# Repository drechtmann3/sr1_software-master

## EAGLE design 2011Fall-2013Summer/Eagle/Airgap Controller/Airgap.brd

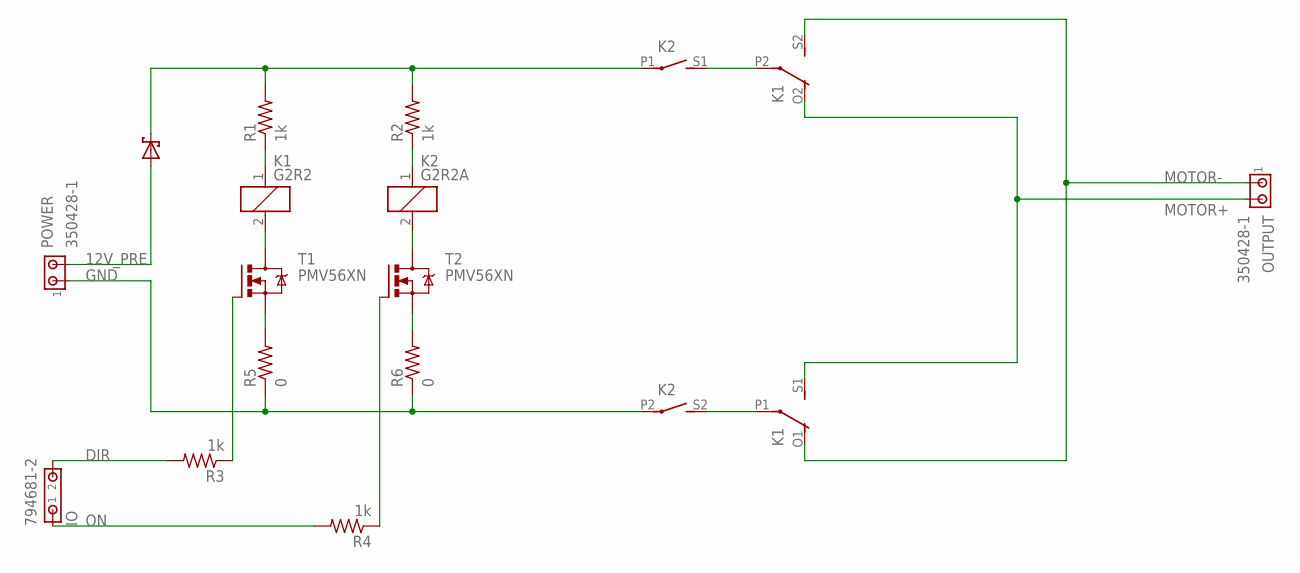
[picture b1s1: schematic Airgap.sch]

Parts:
D3: 6A4; P6T15
IO: 794681-2
K1: G2R2
K2: G2R2A
OUTPUT: 350428-1
POWER: 350428-1
R1, R2, R3, R4: 1k; R1206; PART_NUM CR1206-FX-1001GLF
R5, R6: 0; R1206; PART_NUM CR1206-J/-000ELF
T1, T2: PMV56XN; SOT23

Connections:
12V: D3.C, K2.P1, R1.2, R2.2
12V_PRE: D3.A, POWER.2
DIR: IO.2, R3.2
GND: K2.P2, POWER.1, R5.1, R6.1
MOTOR+: K1.O2 (O), K1.S1 (S), OUTPUT.2
MOTOR-: K1.O1 (O), K1.S2 (S), OUTPUT.1
unnamed: K1.P2, K2.S1 (S)
unnamed: K1.P1, K2.S2 (S)
unnamed: K1.1, R1.1
unnamed: K2.1, R2.1
unnamed: K1.2, T1.3 (D)
unnamed: K2.2, T2.3 (D)
unnamed: R4.1, T2.1 (G)
unnamed: R3.1, T1.1 (G)
unnamed: R5.2, T1.2 (S)
unnamed: R6.2, T2.2 (S)
ON: IO.1, R4.2

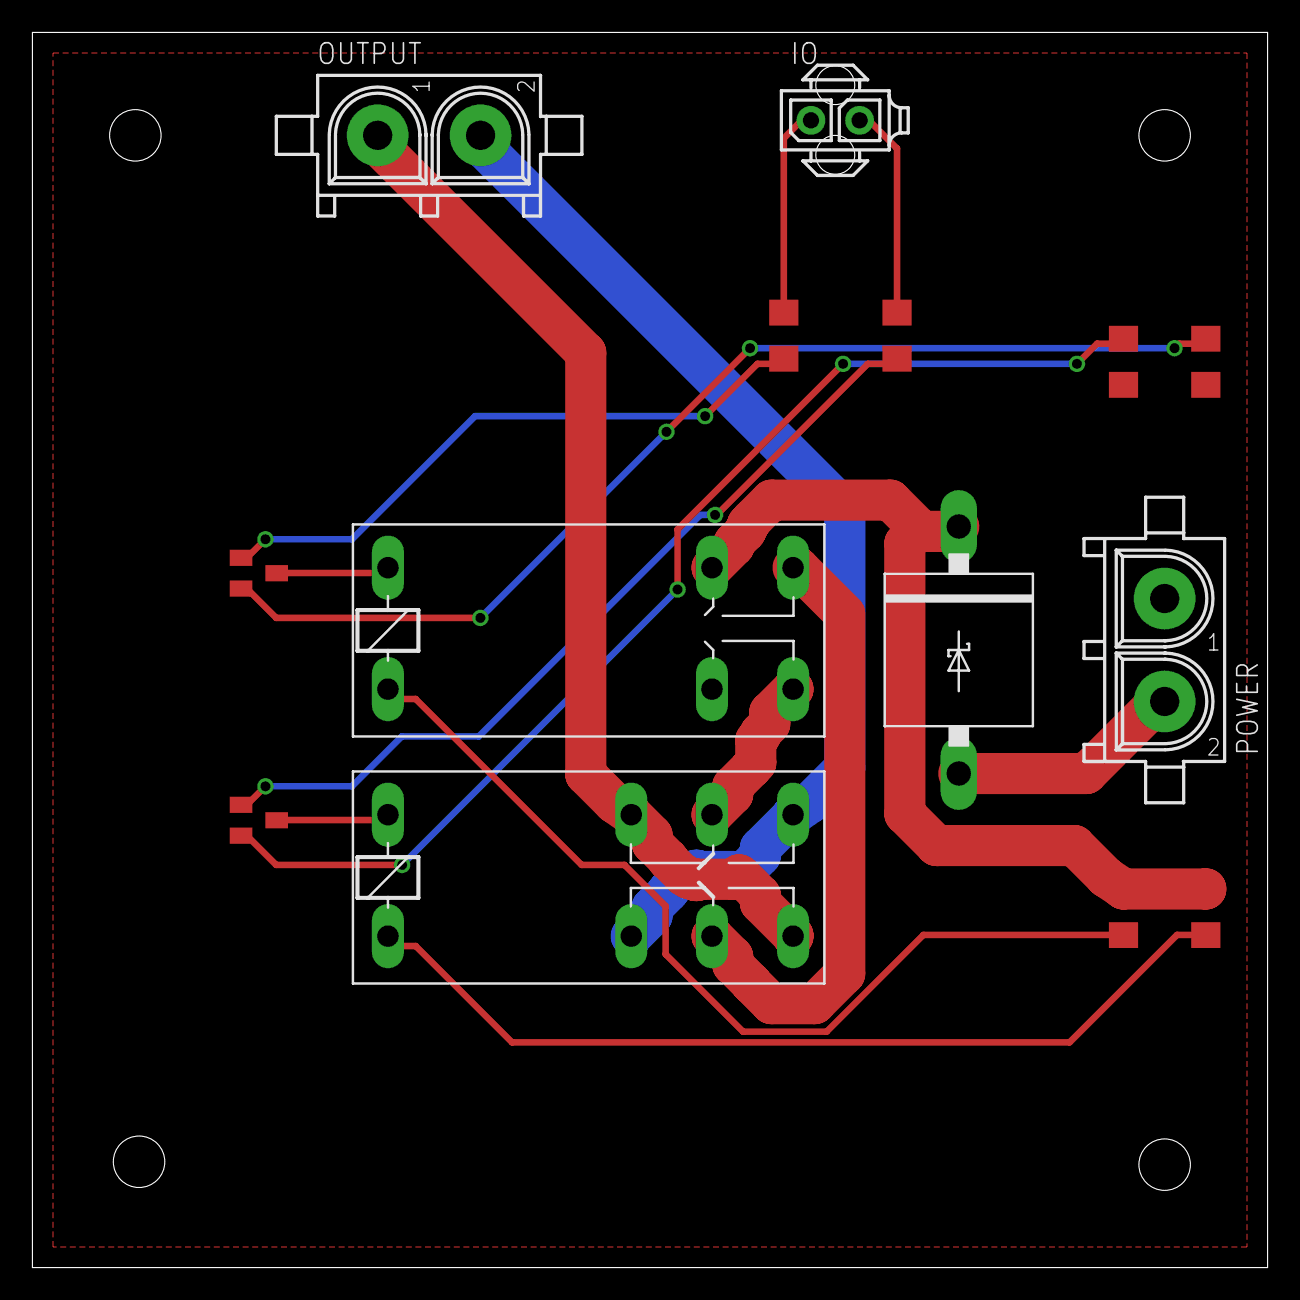
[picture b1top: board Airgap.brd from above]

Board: 2 copper layers, 76.2 x 76.2 mm, 14 parts (0 on the bottom side), 17 nets.

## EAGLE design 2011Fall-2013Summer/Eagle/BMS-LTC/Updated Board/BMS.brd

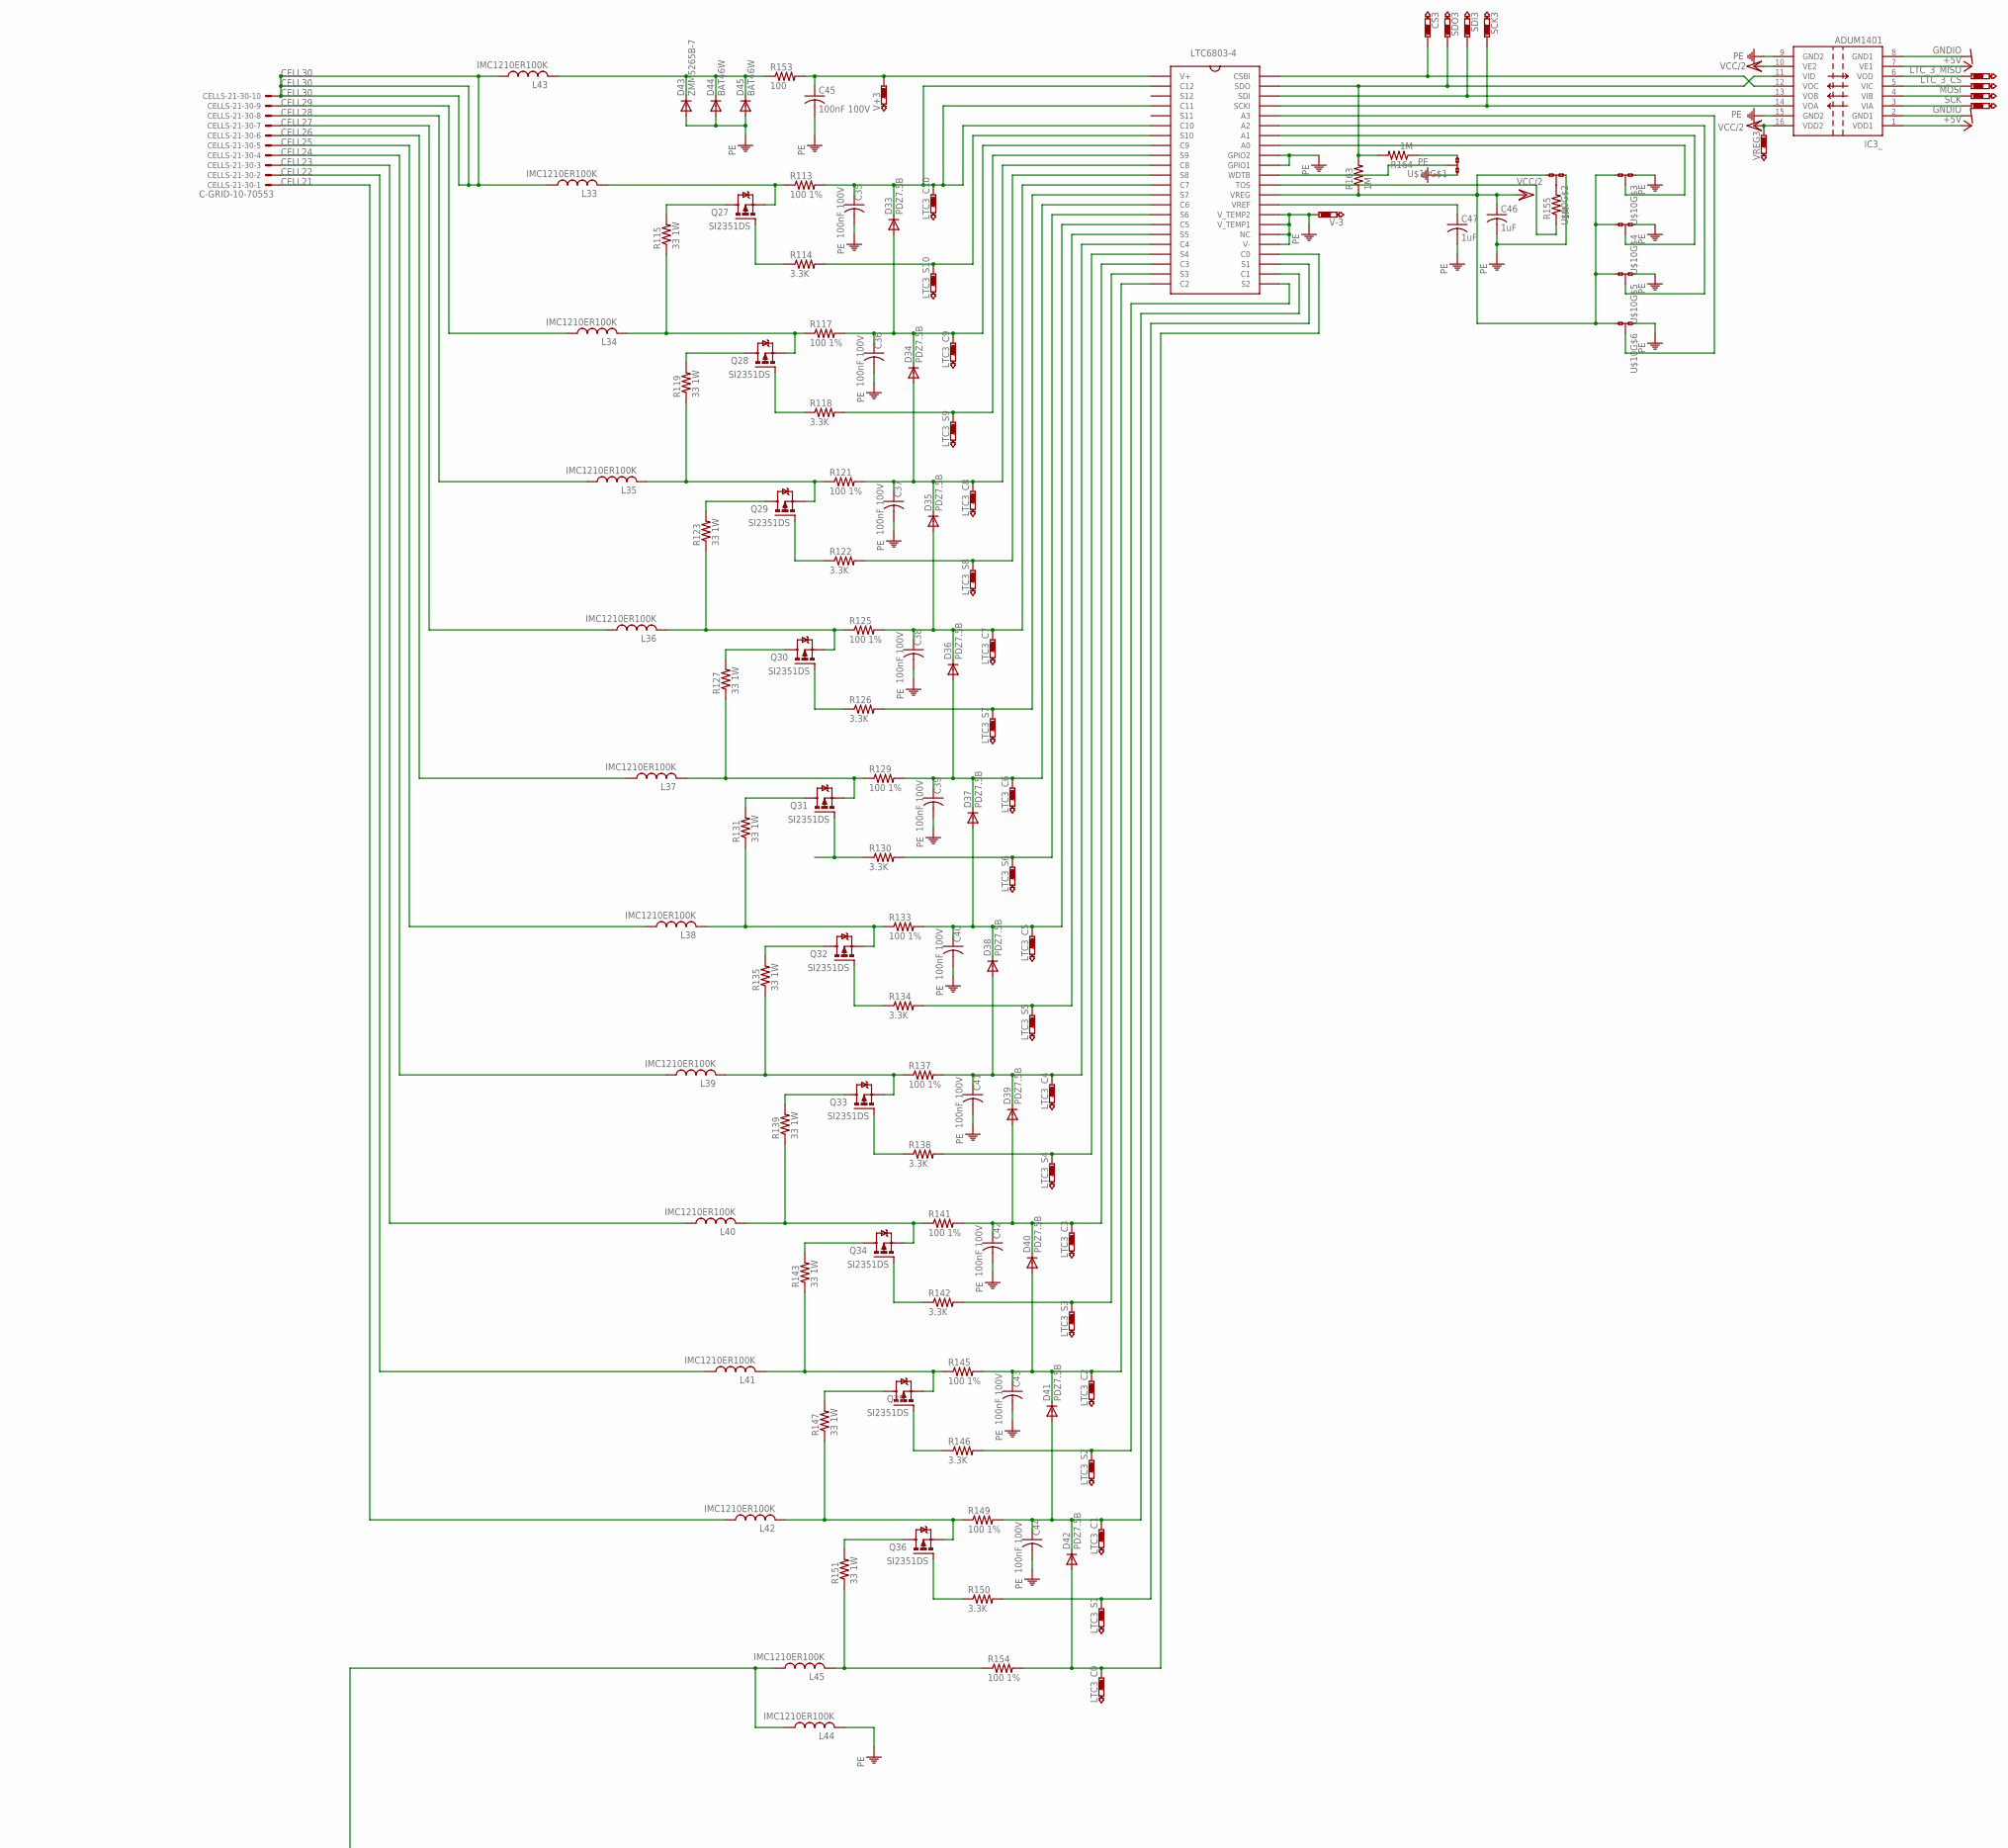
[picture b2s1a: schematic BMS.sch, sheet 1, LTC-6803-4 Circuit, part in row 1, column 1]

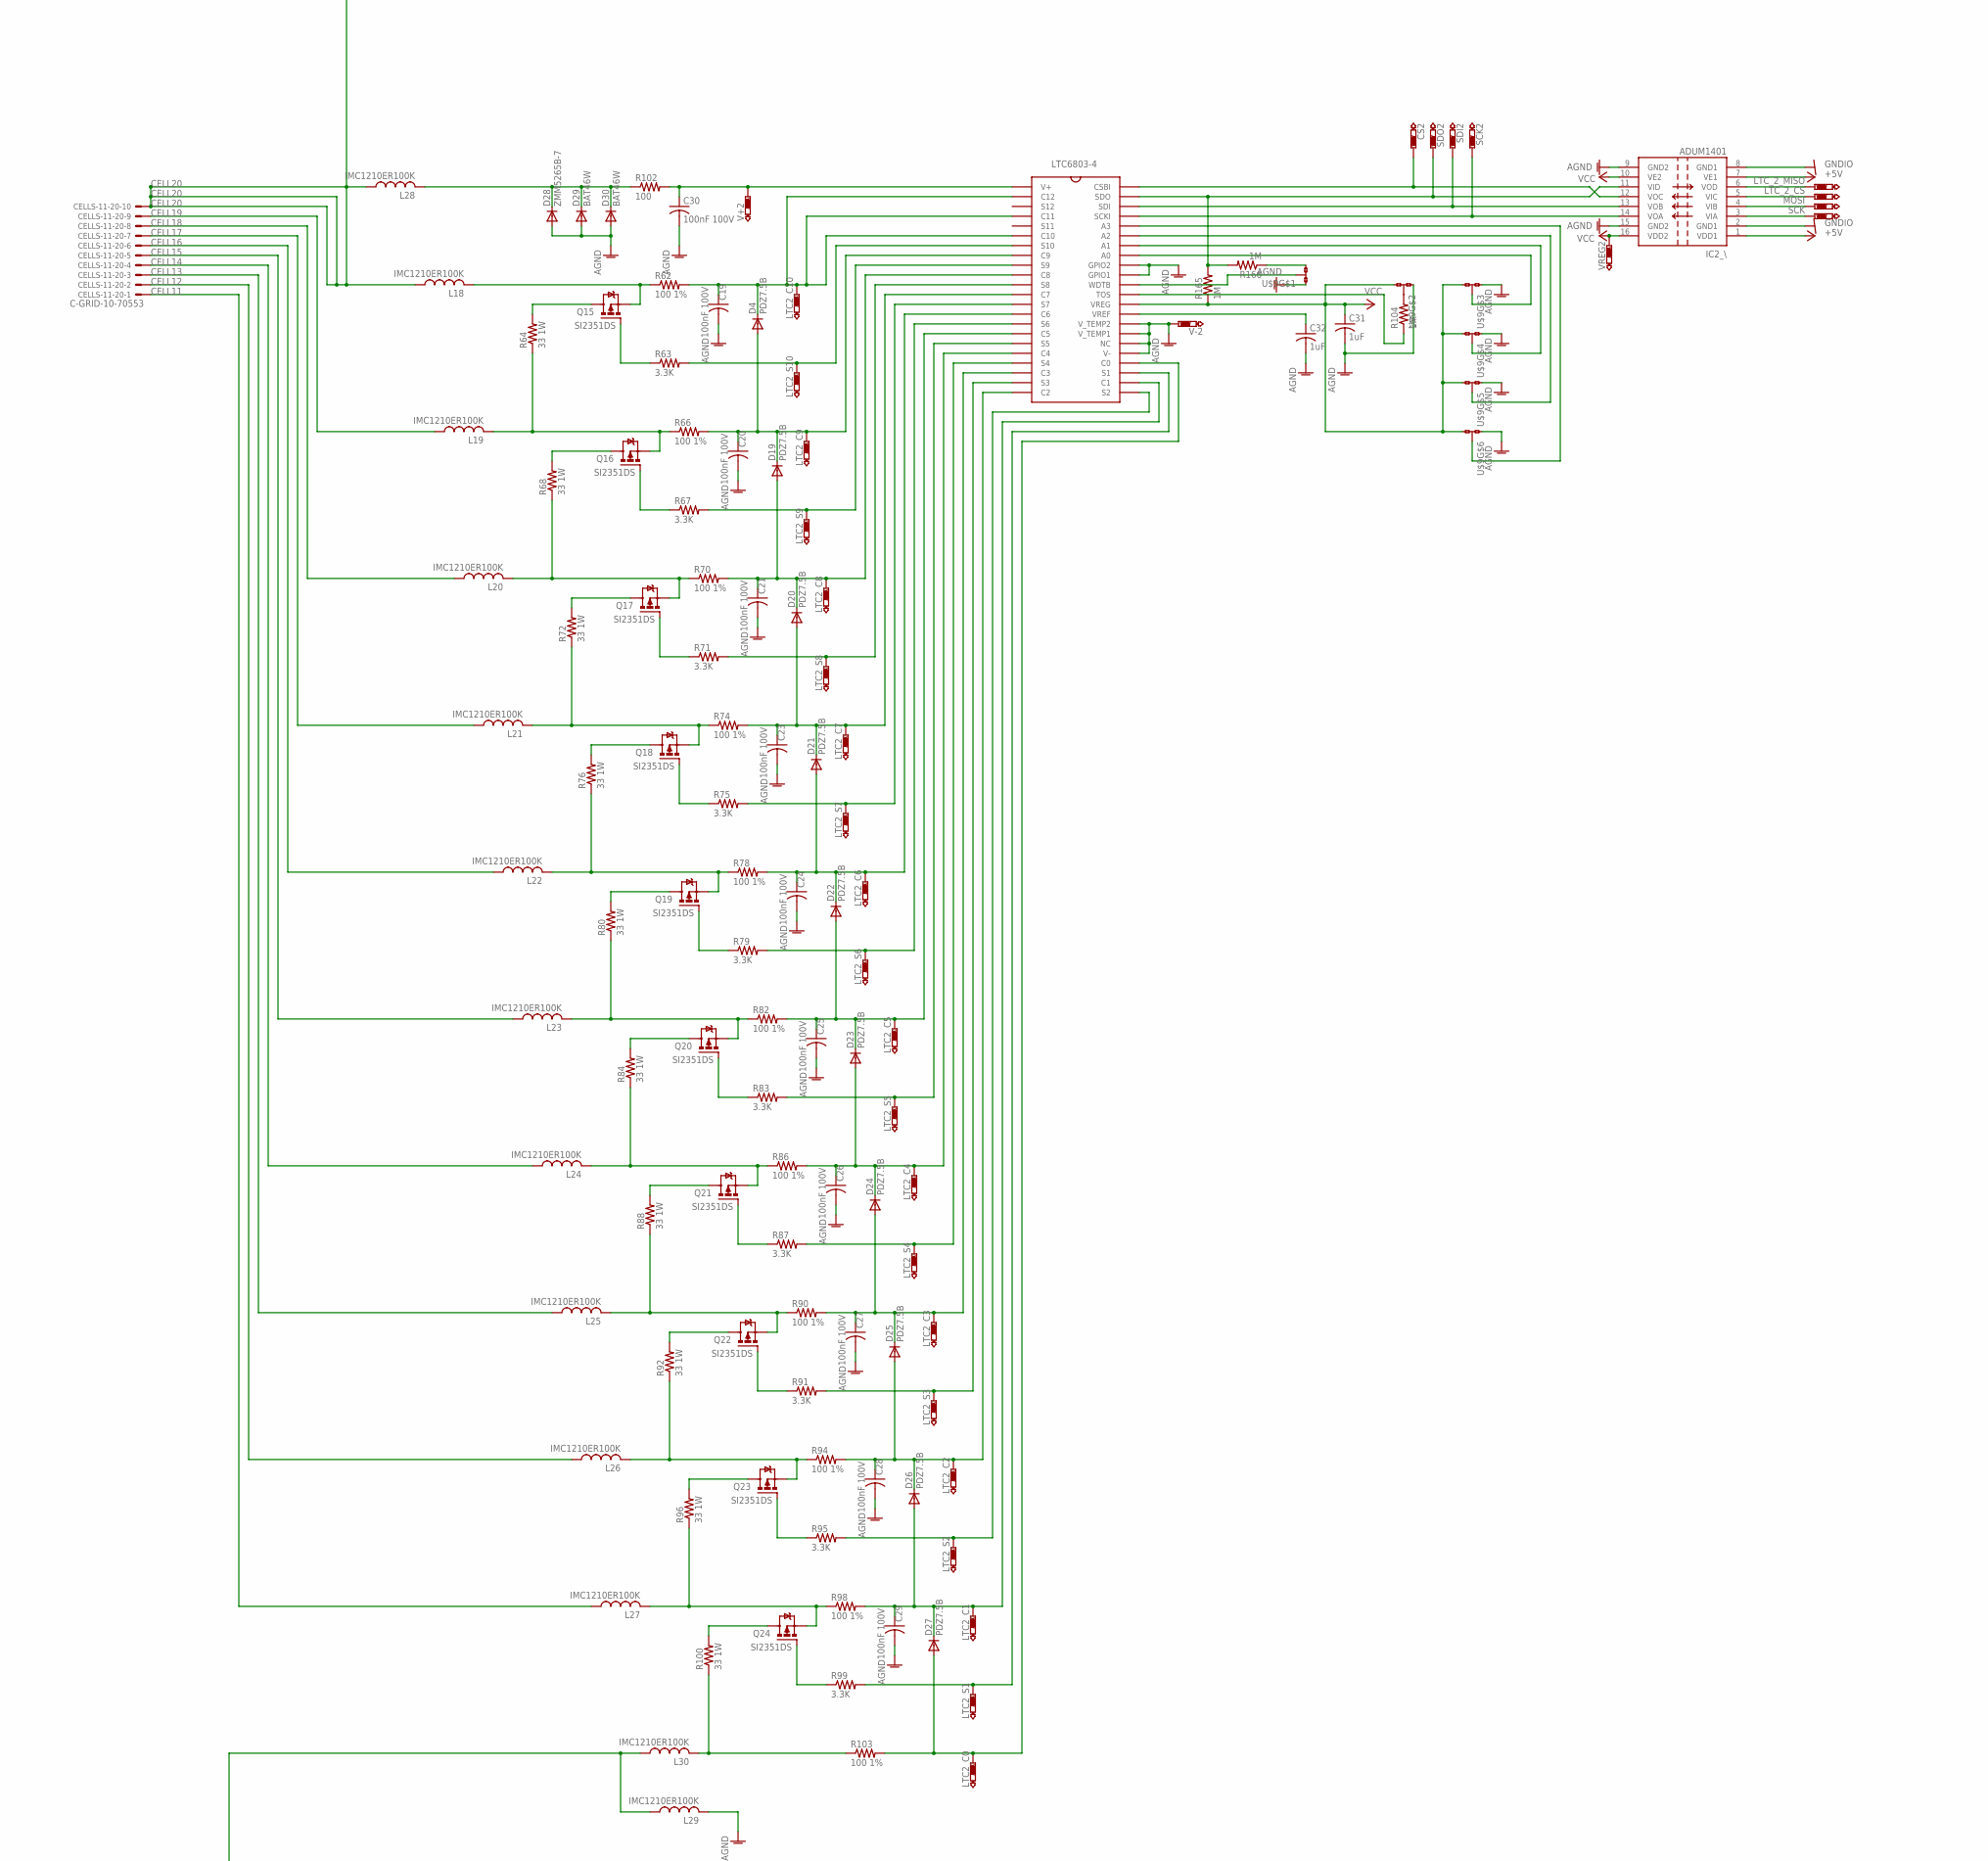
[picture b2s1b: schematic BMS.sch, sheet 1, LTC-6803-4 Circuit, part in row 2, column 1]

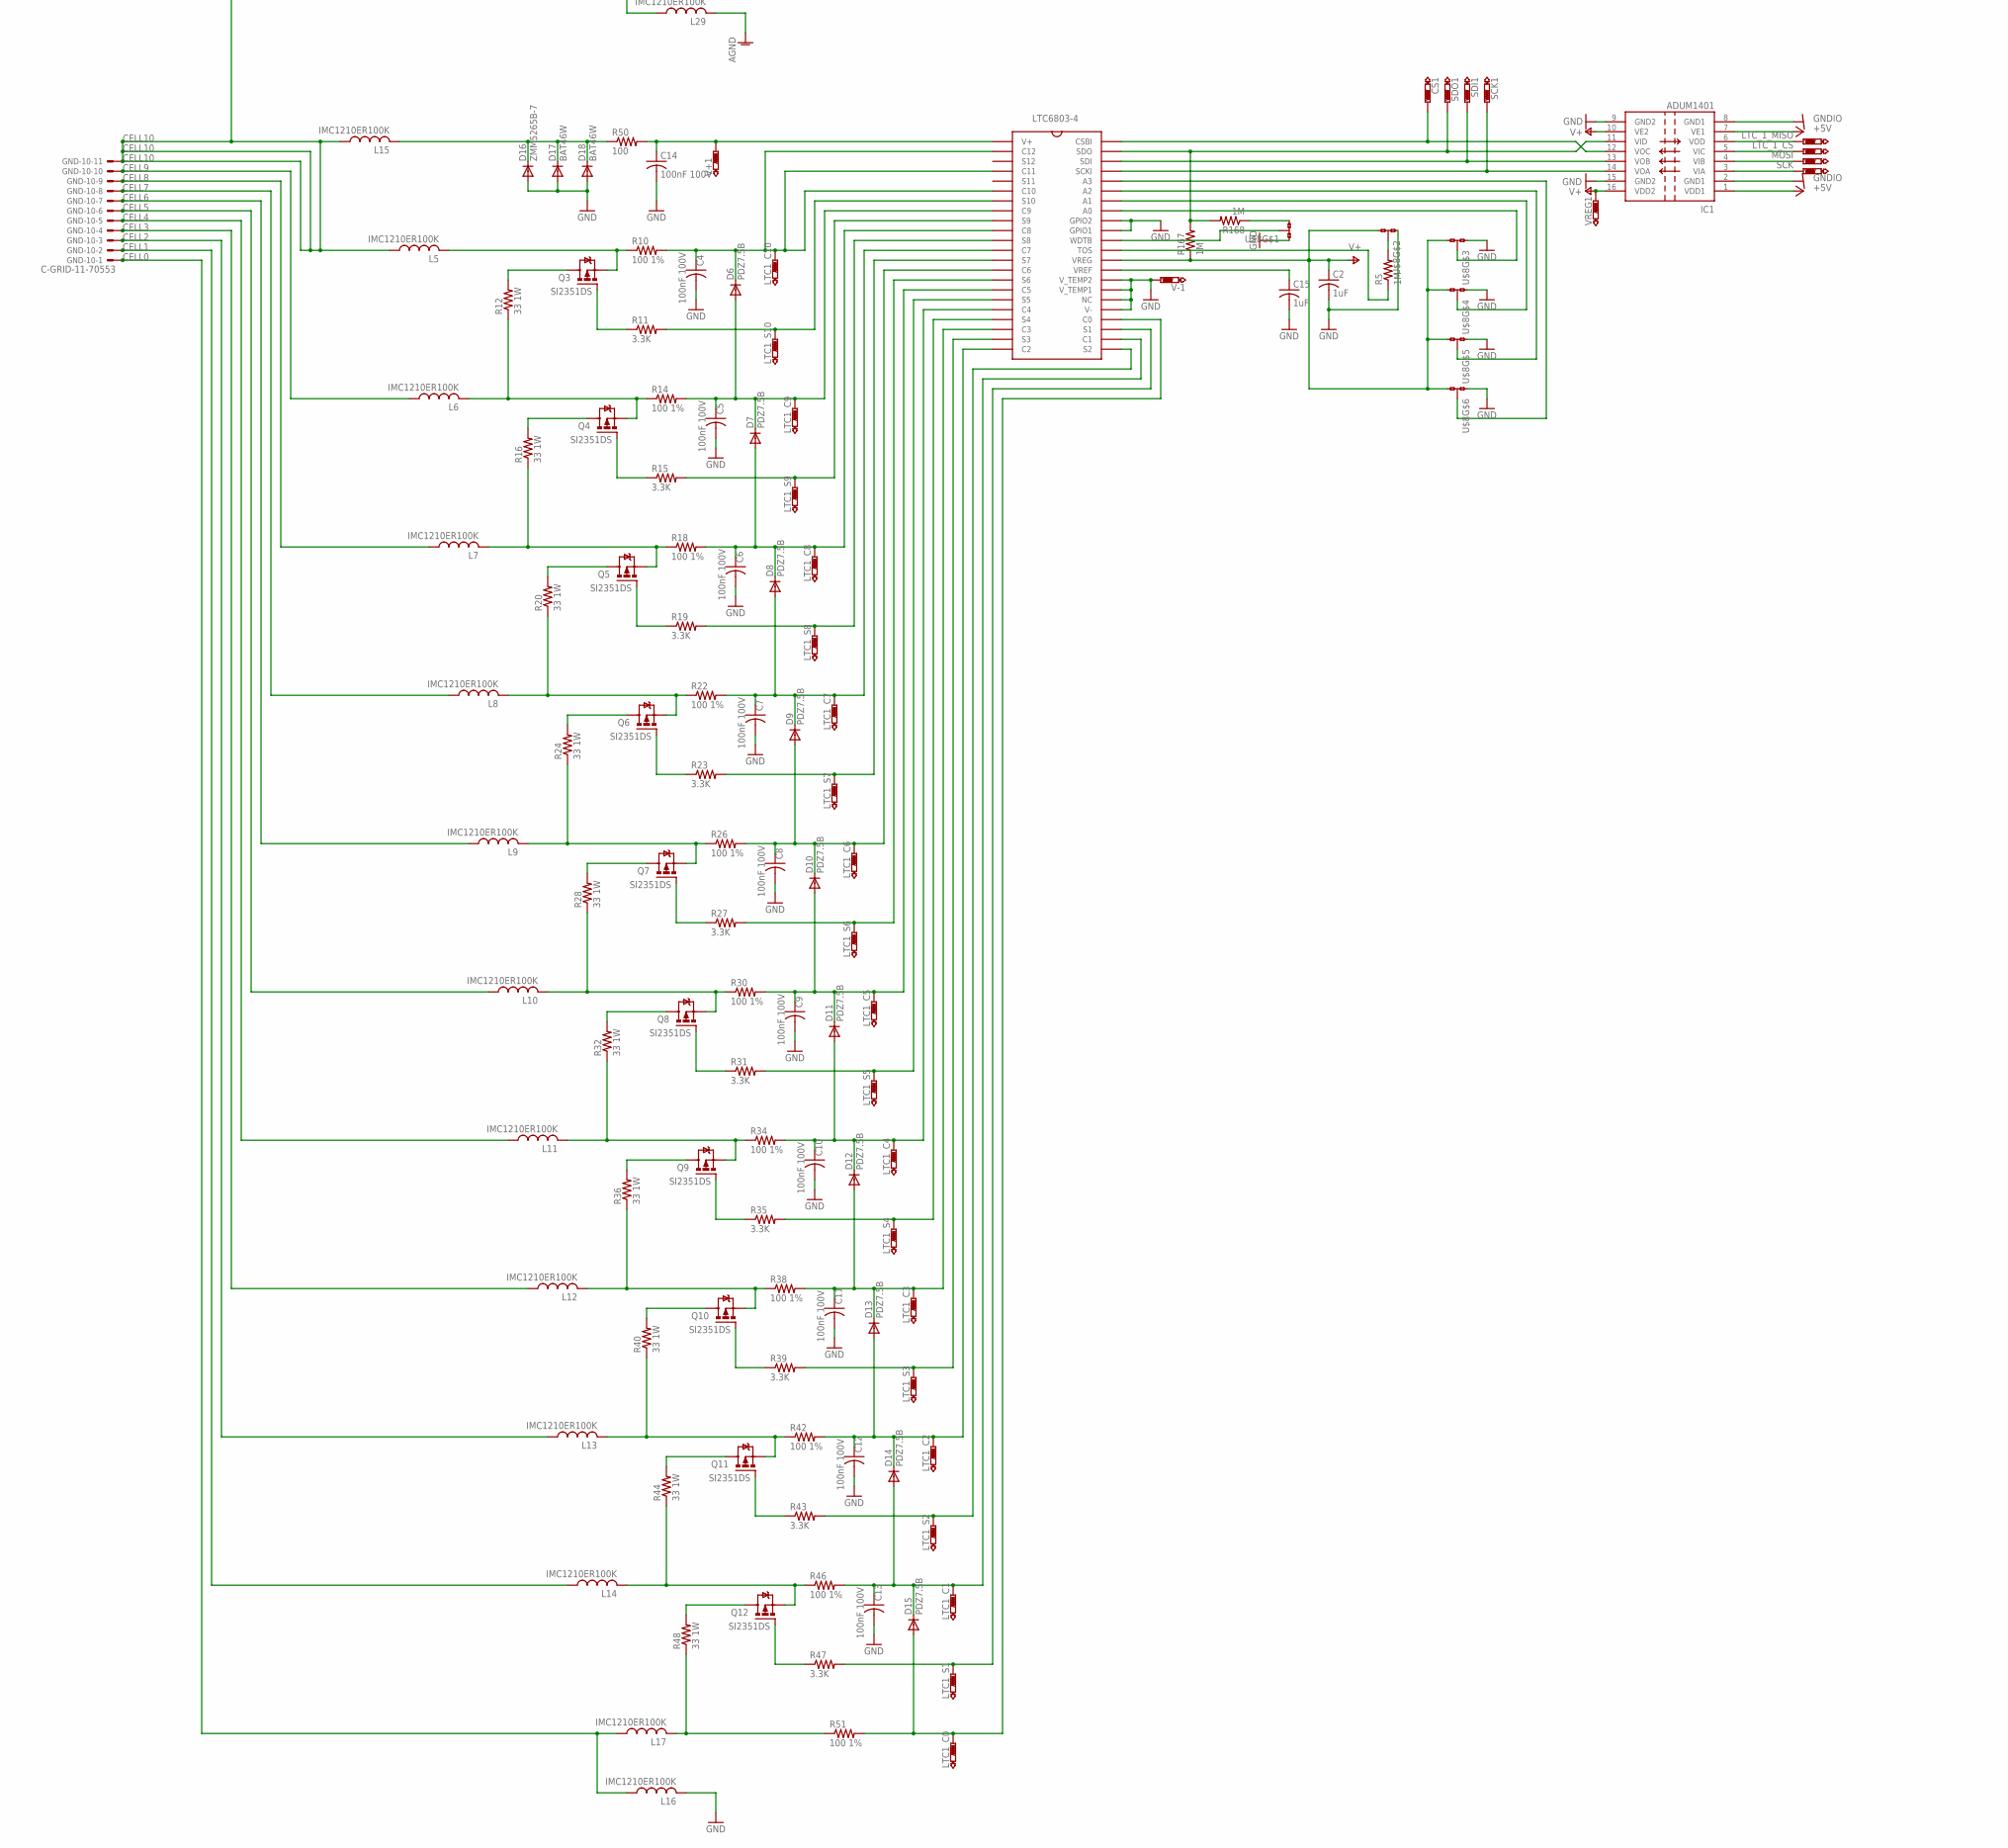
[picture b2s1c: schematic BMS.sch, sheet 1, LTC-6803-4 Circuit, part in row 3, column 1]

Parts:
C2, C15, C31, C32, C46, C47: 1uF; C1206
C4, C5, C6, C7, C8, C9, C10, C11, C12, C13, C14, C19, C20, C21, C23, C24, C25, C26, C27, C28, C29, C30, C35, C36, C37, C38, C39, C40, C41, C42, C43, C44, C45: 100nF 100V; C1206
CELLS-11-20, CELLS-21-30: C-GRID-10-70553; 70553-10
CS1, CS1_O, CS2, CS2_O, CS3, CS3_O: PTR1PAD1-13; P1-13
D4, D6, D7, D8, D9, D10, D11, D12, D13, D14, D15, D19, D20, D21, D22, D23, D24, D25, D26, D27, D33, D34, D35, D36, D37, D38, D39, D40, D41, D42: PDZ7.5B; SOD323-W
D16, D28, D43: ZMM5265B-7; MINIMELF
D17, D18, D29, D30, D44, D45: BAT46W; SOD123
GND-10: C-GRID-11-70553; 70553-11
IC1, IC2_\, IC3_: ADUM1401; SO16W
L5, L6, L7, L8, L9, L10, L11, L12, L13, L14, L15, L16, L17, L18, L19, L20, L21, L22, L23, L24, L25, L26, L27, L28, L29, L30, L33, L34, L35, L36, L37, L38, L39, L40, L41, L42, L43, L44, L45: IMC1210ER100K; L3225M
LTC1, LTC2, LTC3: LTC6803-4; SSOP44
LTC1_C0, LTC1_C1, LTC1_C2, LTC1_C3, LTC1_C4, LTC1_C5, LTC1_C6, LTC1_C7, LTC1_C8, LTC1_C9, LTC1_C10, LTC1_S1, LTC1_S2, LTC1_S3, LTC1_S4, LTC1_S5, LTC1_S6, LTC1_S7, LTC1_S8, LTC1_S9, LTC1_S10, LTC2_C0, LTC2_C1, LTC2_C2, LTC2_C3, LTC2_C4, LTC2_C5, LTC2_C6, LTC2_C7, LTC2_C8, LTC2_C9, LTC2_C10, LTC2_S1, LTC2_S2, LTC2_S3, LTC2_S4, LTC2_S5, LTC2_S6, LTC2_S7, LTC2_S8, LTC2_S9, LTC2_S10, LTC3_C0, LTC3_C1, LTC3_C2, LTC3_C3, LTC3_C4, LTC3_C5, LTC3_C6, LTC3_C7, LTC3_C8, LTC3_C9, LTC3_C10, LTC3_S1, LTC3_S2, LTC3_S3, LTC3_S4, LTC3_S5, LTC3_S6, LTC3_S7, LTC3_S8, LTC3_S9, LTC3_S10: TESTPAD-20MIL; 20MIL
MISO1_O, MISO2_O, MISO3_O: PTR1PAD1-13; P1-13
MOSI1_O, MOSI2_O, MOSI3_O: PTR1PAD1-13; P1-13
Q3, Q4, Q5, Q6, Q7, Q8, Q9, Q10, Q11, Q12, Q15, Q16, Q17, Q18, Q19, Q20, Q21, Q22, Q23, Q24, Q27, Q28, Q29, Q30, Q31, Q32, Q33, Q34, Q35, Q36: SI2351DS; MICRO3
R5, R104, R155, R163, R164, R165, R166, R167, R168: 1M; R1206
R10, R14, R18, R22, R26, R30, R34, R38, R42, R46, R51, R62, R66, R70, R74, R78, R82, R86, R90, R94, R98, R103, R113, R117, R121, R125, R129, R133, R137, R141, R145, R149, R154: 100 1%; R1206
R11, R15, R19, R23, R27, R31, R35, R39, R43, R47, R63, R67, R71, R75, R79, R83, R87, R91, R95, R99, R114, R118, R122, R126, R130, R134, R138, R142, R146, R150: 3.3K; R1206
R12, R16, R20, R24, R28, R32, R36, R40, R44, R48, R64, R68, R72, R76, R80, R84, R88, R92, R96, R100, R115, R119, R123, R127, R131, R135, R139, R143, R147, R151: 33 1W; R2512
R50, R102, R153: 100; R1206
SCK1, SCK1_O, SCK2, SCK2_O, SCK3, SCK3_O: PTR1PAD1-13; P1-13
SDI1, SDI2, SDI3: PTR1PAD1-13; P1-13
SDO1, SDO2, SDO3: PTR1PAD1-13; P1-13
U$8, U$9, U$10: 3ROW_6POS
V+1, V+2, V+3: PTR1PAD1-13; P1-13
V-1, V-2, V-3: PTR1PAD1-13; P1-13
VREG1, VREG2, VREG3: TESTPAD-20MIL; 20MIL

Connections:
+5V: IC1.1 (VDD1), IC1.7 (VE1), IC2_\.1 (VDD1), IC2_\.7 (VE1), IC3_.1 (VDD1), IC3_.7 (VE1); also elsewhere on the board
AGND: C19.2, C20.2, C21.2, C23.2, C24.2, C25.2, C26.2, C27.2, C28.2, C29.2, C30.2, C31.2, C32.2, D28.A, D29.A, D30.A, IC2_\.9 (GND2), IC2_\.15 (GND2), L29.2, LTC2.P$27 (V-), LTC2.P$28 (NC), LTC2.P$29 (V_TEMP1), LTC2.P$30 (V_TEMP2), LTC2.P$35 (GPIO1), LTC2.P$36 (GPIO2), U$9.1, U$9.4 (1), U$9.7 (1), U$9.10 (1), U$9.13 (1), U$9.16 (1), V-2.TP
CELL0: GND-10.1, L16.1, L17.1
CELL1: GND-10.2, L14.1
CELL2: GND-10.3, L13.1
CELL3: GND-10.4, L12.1
CELL4: GND-10.5, L11.1
CELL5: GND-10.6, L10.1
CELL6: GND-10.7, L9.1
CELL7: GND-10.8, L8.1
CELL8: GND-10.9, L7.1
CELL9: GND-10.10, L6.1
CELL10: GND-10.11, L5.1, L15.1, L29.1, L30.1
CELL11: CELLS-11-20.1, L27.1
CELL12: CELLS-11-20.2, L26.1
CELL13: CELLS-11-20.3, L25.1
CELL14: CELLS-11-20.4, L24.1
CELL15: CELLS-11-20.5, L23.1
CELL16: CELLS-11-20.6, L22.1
CELL17: CELLS-11-20.7, L21.1
CELL18: CELLS-11-20.8, L20.1
CELL19: CELLS-11-20.9, L19.1
CELL20: CELLS-11-20.10, L18.1, L28.1, L44.1, L45.1
CELL21: CELLS-21-30.1, L42.1
CELL22: CELLS-21-30.2, L41.1
CELL23: CELLS-21-30.3, L40.1
CELL24: CELLS-21-30.4, L39.1
CELL25: CELLS-21-30.5, L38.1
CELL26: CELLS-21-30.6, L37.1
CELL27: CELLS-21-30.7, L36.1
CELL28: CELLS-21-30.8, L35.1
CELL29: CELLS-21-30.9, L34.1
CELL30: CELLS-21-30.10, L33.1, L43.1
GND: C2.2, C4.2, C5.2, C6.2, C7.2, C8.2, C9.2, C10.2, C11.2, C12.2, C13.2, C14.2, C15.2, D16.A, D17.A, D18.A, IC1.9 (GND2), IC1.15 (GND2), L16.2, LTC1.P$27 (V-), LTC1.P$28 (NC), LTC1.P$29 (V_TEMP1), LTC1.P$30 (V_TEMP2), LTC1.P$35 (GPIO1), LTC1.P$36 (GPIO2), U$8.1, U$8.4 (1), U$8.7 (1), U$8.10 (1), U$8.13 (1), U$8.16 (1), V-1.TP
GNDIO: IC1.2 (GND1), IC1.8 (GND1), IC2_\.2 (GND1), IC2_\.8 (GND1), IC3_.2 (GND1), IC3_.8 (GND1); also elsewhere on the board
LTC_1_CS: CS1_O.TP, IC1.5 (VIC); also elsewhere on the board
LTC_1_MISO: IC1.6 (VOD), MISO1_O.TP; also elsewhere on the board
LTC_2_CS: CS2_O.TP, IC2_\.5 (VIC); also elsewhere on the board
LTC_2_MISO: IC2_\.6 (VOD), MISO2_O.TP; also elsewhere on the board
LTC_3_CS: CS3_O.TP, IC3_.5 (VIC); also elsewhere on the board
LTC_3_MISO: IC3_.6 (VOD), MISO3_O.TP; also elsewhere on the board
MOSI: IC1.4 (VIB), IC2_\.4 (VIB), IC3_.4 (VIB), MOSI1_O.TP, MOSI2_O.TP, MOSI3_O.TP; also elsewhere on the board
unnamed: R104.2, U$9.5 (2)
unnamed: R155.2, U$10.5 (2)
unnamed: C4.1, D6.C, LTC1.P$2 (C12), LTC1.P$4 (C11), LTC1.P$6 (C10), LTC1_C10.P$1, R10.2
unnamed: R5.2, U$8.5 (2)
unnamed: LTC1.P$33 (TOS), R5.1
unnamed: LTC1.P$38 (A1), U$8.11 (2)
unnamed: LTC1.P$39 (A2), U$8.14 (2)
unnamed: LTC1.P$40 (A3), U$8.17 (2)
unnamed: LTC1.P$37 (A0), U$8.8 (2)
unnamed: L5.2, Q3.2 (S), R10.1
unnamed: CS1.TP, IC1.12 (VOC), LTC1.P$44 (CSBI)
unnamed: IC1.13 (VOB), LTC1.P$42 (SDI), SDI1.TP
unnamed: IC1.14 (VOA), LTC1.P$41 (SCKI), SCK1.TP
unnamed: LTC1.P$7 (S10), LTC1_S10.P$1, R11.2
unnamed: Q3.1 (G), R11.1
unnamed: Q3.3 (D), R12.2
unnamed: L6.2, Q4.2 (S), R12.1, R14.1
unnamed: C15.1, LTC1.P$31 (VREF)
unnamed: C5.1, D6.A, D7.C, LTC1.P$8 (C9), LTC1_C9.P$1, R14.2
unnamed: LTC1.P$9 (S9), LTC1_S9.P$1, R15.2
unnamed: Q4.1 (G), R15.1
unnamed: Q4.3 (D), R16.2
unnamed: L7.2, Q5.2 (S), R16.1, R18.1
unnamed: C6.1, D7.A, D8.C, LTC1.P$10 (C8), LTC1_C8.P$1, R18.2
unnamed: LTC1.P$11 (S8), LTC1_S8.P$1, R19.2
unnamed: Q5.1 (G), R19.1
unnamed: Q5.3 (D), R20.2
unnamed: L8.2, Q6.2 (S), R20.1, R22.1
unnamed: C7.1, D8.A, D9.C, LTC1.P$12 (C7), LTC1_C7.P$1, R22.2
unnamed: LTC1.P$13 (S7), LTC1_S7.P$1, R23.2
unnamed: Q6.1 (G), R23.1
unnamed: Q6.3 (D), R24.2
unnamed: L9.2, Q7.2 (S), R24.1, R26.1
unnamed: C8.1, D9.A, D10.C, LTC1.P$14 (C6), LTC1_C6.P$1, R26.2
unnamed: C19.1, D4.C, LTC2.P$2 (C12), LTC2.P$4 (C11), LTC2.P$6 (C10), LTC2_C10.P$1, R62.2
unnamed: LTC1.P$15 (S6), LTC1_S6.P$1, R27.2
unnamed: Q7.1 (G), R27.1
unnamed: Q7.3 (D), R28.2
unnamed: L10.2, Q8.2 (S), R28.1, R30.1
unnamed: C9.1, D10.A, D11.C, LTC1.P$16 (C5), LTC1_C5.P$1, R30.2
unnamed: LTC1.P$17 (S5), LTC1_S5.P$1, R31.2
unnamed: Q8.1 (G), R31.1
unnamed: Q8.3 (D), R32.2
unnamed: L11.2, Q9.2 (S), R32.1, R34.1
unnamed: L18.2, Q15.2 (S), R62.1
unnamed: C10.1, D11.A, D12.C, LTC1.P$18 (C4), LTC1_C4.P$1, R34.2
unnamed: LTC2.P$7 (S10), LTC2_S10.P$1, R63.2
unnamed: LTC1.P$19 (S4), LTC1_S4.P$1, R35.2
unnamed: Q9.1 (G), R35.1
unnamed: Q9.3 (D), R36.2
unnamed: L12.2, Q10.2 (S), R36.1, R38.1
unnamed: Q15.1 (G), R63.1
unnamed: C11.1, D12.A, D13.C, LTC1.P$20 (C3), LTC1_C3.P$1, R38.2
unnamed: Q15.3 (D), R64.2
unnamed: LTC1.P$21 (S3), LTC1_S3.P$1, R39.2
unnamed: Q10.1 (G), R39.1
unnamed: Q10.3 (D), R40.2
unnamed: L13.2, Q11.2 (S), R40.1, R42.1
unnamed: L19.2, Q16.2 (S), R64.1, R66.1
unnamed: C12.1, D13.A, D14.C, LTC1.P$22 (C2), LTC1_C2.P$1, R42.2
unnamed: C20.1, D4.A, D19.C, LTC2.P$8 (C9), LTC2_C9.P$1, R66.2
unnamed: LTC2.P$9 (S9), LTC2_S9.P$1, R67.2
unnamed: LTC1.P$23 (S2), LTC1_S2.P$1, R43.2
unnamed: Q11.1 (G), R43.1
unnamed: Q11.3 (D), R44.2
unnamed: L14.2, Q12.2 (S), R44.1, R46.1
unnamed: Q16.1 (G), R67.1
unnamed: C13.1, D14.A, D15.C, LTC1.P$24 (C1), LTC1_C1.P$1, R46.2
unnamed: Q16.3 (D), R68.2
unnamed: LTC1.P$25 (S1), LTC1_S1.P$1, R47.2
unnamed: Q12.1 (G), R47.1
unnamed: Q12.3 (D), R48.2
unnamed: L17.2, R48.1, R51.1
unnamed: L20.2, Q17.2 (S), R68.1, R70.1
unnamed: D15.A, LTC1.P$26 (C0), LTC1_C0.P$1, R51.2
unnamed: C21.1, D19.A, D20.C, LTC2.P$10 (C8), LTC2_C8.P$1, R70.2
unnamed: D16.C, D17.C, D18.C, L15.2, R50.1
unnamed: C14.1, LTC1.P$1 (V+), R50.2, V+1.TP
unnamed: LTC2.P$11 (S8), LTC2_S8.P$1, R71.2
unnamed: Q17.1 (G), R71.1
unnamed: Q17.3 (D), R72.2
unnamed: L21.2, Q18.2 (S), R72.1, R74.1
unnamed: C23.1, D20.A, D21.C, LTC2.P$12 (C7), LTC2_C7.P$1, R74.2
unnamed: LTC2.P$13 (S7), LTC2_S7.P$1, R75.2
unnamed: Q18.1 (G), R75.1
unnamed: Q18.3 (D), R76.2
unnamed: L22.2, Q19.2 (S), R76.1, R78.1
unnamed: C24.1, D21.A, D22.C, LTC2.P$14 (C6), LTC2_C6.P$1, R78.2
unnamed: LTC2.P$15 (S6), LTC2_S6.P$1, R79.2
unnamed: Q19.1 (G), R79.1
unnamed: Q19.3 (D), R80.2
unnamed: L23.2, Q20.2 (S), R80.1, R82.1
unnamed: C25.1, D22.A, D23.C, LTC2.P$16 (C5), LTC2_C5.P$1, R82.2
unnamed: LTC2.P$17 (S5), LTC2_S5.P$1, R83.2
unnamed: Q20.1 (G), R83.1
unnamed: Q20.3 (D), R84.2
unnamed: L24.2, Q21.2 (S), R84.1, R86.1
unnamed: C26.1, D23.A, D24.C, LTC2.P$18 (C4), LTC2_C4.P$1, R86.2
unnamed: LTC2.P$19 (S4), LTC2_S4.P$1, R87.2
unnamed: Q21.1 (G), R87.1
unnamed: Q21.3 (D), R88.2
unnamed: L25.2, Q22.2 (S), R88.1, R90.1
unnamed: C27.1, D24.A, D25.C, LTC2.P$20 (C3), LTC2_C3.P$1, R90.2
unnamed: LTC2.P$21 (S3), LTC2_S3.P$1, R91.2
unnamed: Q22.1 (G), R91.1
unnamed: Q22.3 (D), R92.2
unnamed: L26.2, Q23.2 (S), R92.1, R94.1
unnamed: C28.1, D25.A, D26.C, LTC2.P$22 (C2), LTC2_C2.P$1, R94.2
unnamed: LTC2.P$23 (S2), LTC2_S2.P$1, R95.2
unnamed: Q23.1 (G), R95.1
unnamed: Q23.3 (D), R96.2
unnamed: L27.2, Q24.2 (S), R96.1, R98.1
unnamed: C29.1, D26.A, D27.C, LTC2.P$24 (C1), LTC2_C1.P$1, R98.2
unnamed: LTC2.P$25 (S1), LTC2_S1.P$1, R99.2
unnamed: Q24.1 (G), R99.1
unnamed: Q24.3 (D), R100.2
unnamed: L30.2, R100.1, R103.1
unnamed: D27.A, LTC2.P$26 (C0), LTC2_C0.P$1, R103.2
unnamed: D28.C, D29.C, D30.C, L28.2, R102.1
unnamed: C30.1, LTC2.P$1 (V+), R102.2, V+2.TP
unnamed: LTC2.P$33 (TOS), R104.1
unnamed: LTC2.P$39 (A2), U$9.14 (2)
unnamed: LTC2.P$40 (A3), U$9.17 (2)
unnamed: LTC2.P$38 (A1), U$9.11 (2)
unnamed: LTC2.P$37 (A0), U$9.8 (2)
unnamed: CS2.TP, IC2_\.12 (VOC), LTC2.P$44 (CSBI)
unnamed: IC2_\.13 (VOB), LTC2.P$42 (SDI), SDI2.TP
unnamed: IC2_\.14 (VOA), LTC2.P$41 (SCKI), SCK2.TP
unnamed: C32.1, LTC2.P$31 (VREF)
unnamed: C35.1, D33.C, LTC3.P$2 (C12), LTC3.P$4 (C11), LTC3.P$6 (C10), LTC3_C10.P$1, R113.2
unnamed: L33.2, Q27.2 (S), R113.1
unnamed: LTC3.P$7 (S10), LTC3_S10.P$1, R114.2
unnamed: Q27.1 (G), R114.1
unnamed: Q27.3 (D), R115.2
unnamed: L34.2, Q28.2 (S), R115.1, R117.1
unnamed: C36.1, D33.A, D34.C, LTC3.P$8 (C9), LTC3_C9.P$1, R117.2
unnamed: LTC3.P$9 (S9), LTC3_S9.P$1, R118.2
unnamed: Q28.1 (G), R118.1
unnamed: Q28.3 (D), R119.2
unnamed: L35.2, Q29.2 (S), R119.1, R121.1
unnamed: C37.1, D34.A, D35.C, LTC3.P$10 (C8), LTC3_C8.P$1, R121.2
unnamed: LTC3.P$11 (S8), LTC3_S8.P$1, R122.2
unnamed: Q29.1 (G), R122.1
unnamed: Q29.3 (D), R123.2
unnamed: L36.2, Q30.2 (S), R123.1, R125.1
unnamed: C38.1, D35.A, D36.C, LTC3.P$12 (C7), LTC3_C7.P$1, R125.2
unnamed: LTC3.P$13 (S7), LTC3_S7.P$1, R126.2
unnamed: Q30.1 (G), R126.1
unnamed: Q30.3 (D), R127.2
unnamed: L37.2, Q31.2 (S), R127.1, R129.1
unnamed: C39.1, D36.A, D37.C, LTC3.P$14 (C6), LTC3_C6.P$1, R129.2
unnamed: LTC3.P$15 (S6), LTC3_S6.P$1, R130.2
unnamed: Q31.1 (G), R130.1
unnamed: Q31.3 (D), R131.2
unnamed: L38.2, Q32.2 (S), R131.1, R133.1
unnamed: C40.1, D37.A, D38.C, LTC3.P$16 (C5), LTC3_C5.P$1, R133.2
unnamed: LTC3.P$17 (S5), LTC3_S5.P$1, R134.2
unnamed: Q32.1 (G), R134.1
unnamed: Q32.3 (D), R135.2
unnamed: L39.2, Q33.2 (S), R135.1, R137.1
unnamed: C41.1, D38.A, D39.C, LTC3.P$18 (C4), LTC3_C4.P$1, R137.2
unnamed: LTC3.P$19 (S4), LTC3_S4.P$1, R138.2
unnamed: Q33.1 (G), R138.1
unnamed: Q33.3 (D), R139.2
unnamed: L40.2, Q34.2 (S), R139.1, R141.1
unnamed: C42.1, D39.A, D40.C, LTC3.P$20 (C3), LTC3_C3.P$1, R141.2
unnamed: LTC3.P$21 (S3), LTC3_S3.P$1, R142.2
unnamed: Q34.1 (G), R142.1
unnamed: Q34.3 (D), R143.2
unnamed: L41.2, Q35.2 (S), R143.1, R145.1
unnamed: C43.1, D40.A, D41.C, LTC3.P$22 (C2), LTC3_C2.P$1, R145.2
unnamed: LTC3.P$23 (S2), LTC3_S2.P$1, R146.2
unnamed: Q35.1 (G), R146.1
unnamed: Q35.3 (D), R147.2
unnamed: L42.2, Q36.2 (S), R147.1, R149.1
unnamed: C44.1, D41.A, D42.C, LTC3.P$24 (C1), LTC3_C1.P$1, R149.2
unnamed: LTC3.P$25 (S1), LTC3_S1.P$1, R150.2
unnamed: Q36.1 (G), R150.1
unnamed: Q36.3 (D), R151.2
unnamed: L45.2, R151.1, R154.1
unnamed: D42.A, LTC3.P$26 (C0), LTC3_C0.P$1, R154.2
unnamed: D43.C, D44.C, D45.C, L43.2, R153.1
unnamed: C45.1, LTC3.P$1 (V+), R153.2, V+3.TP
unnamed: LTC3.P$33 (TOS), R155.1
unnamed: LTC3.P$39 (A2), U$10.14 (2)
unnamed: LTC3.P$40 (A3), U$10.17 (2)
unnamed: LTC3.P$38 (A1), U$10.11 (2)
unnamed: LTC3.P$37 (A0), U$10.8 (2)
unnamed: CS3.TP, IC3_.12 (VOC), LTC3.P$44 (CSBI)
unnamed: IC3_.13 (VOB), LTC3.P$42 (SDI), SDI3.TP
unnamed: IC3_.14 (VOA), LTC3.P$41 (SCKI), SCK3.TP
unnamed: C47.1, LTC3.P$31 (VREF)
unnamed: IC1.11 (VID), LTC1.P$43 (SDO), R167.2, R168.2, SDO1.TP
unnamed: R168.1, U$8.3
unnamed: LTC1.P$34 (WDTB), U$8.2
unnamed: IC2_\.11 (VID), LTC2.P$43 (SDO), R165.2, R166.2, SDO2.TP
unnamed: R166.1, U$9.3
unnamed: LTC2.P$34 (WDTB), U$9.2
unnamed: LTC3.P$34 (WDTB), U$10.2
unnamed: IC3_.11 (VID), LTC3.P$43 (SDO), R163.2, R164.2, SDO3.TP
unnamed: R164.1, U$10.3
PE: C35.2, C36.2, C37.2, C38.2, C39.2, C40.2, C41.2, C42.2, C43.2, C44.2, C45.2, C46.2, C47.2, D43.A, D44.A, D45.A, IC3_.9 (GND2), IC3_.15 (GND2), L44.2, LTC3.P$27 (V-), LTC3.P$28 (NC), LTC3.P$29 (V_TEMP1), LTC3.P$30 (V_TEMP2), LTC3.P$35 (GPIO1), LTC3.P$36 (GPIO2), U$10.1, U$10.4 (1), U$10.7 (1), U$10.10 (1), U$10.13 (1), U$10.16 (1), V-3.TP
SCK: IC1.3 (VIA), IC2_\.3 (VIA), IC3_.3 (VIA), SCK1_O.TP, SCK2_O.TP, SCK3_O.TP; also elsewhere on the board
V+: C2.1, IC1.10 (VE2), IC1.16 (VDD2), LTC1.P$32 (VREG), R167.1, U$8.6 (3), U$8.9 (3), U$8.12 (3), U$8.15 (3), U$8.18 (3), VREG1.P$1
VCC: C31.1, IC2_\.10 (VE2), IC2_\.16 (VDD2), LTC2.P$32 (VREG), R165.1, U$9.6 (3), U$9.9 (3), U$9.12 (3), U$9.15 (3), U$9.18 (3), VREG2.P$1
VCC/2: C46.1, IC3_.10 (VE2), IC3_.16 (VDD2), LTC3.P$32 (VREG), R163.1, U$10.6 (3), U$10.9 (3), U$10.12 (3), U$10.15 (3), U$10.18 (3), VREG3.P$1

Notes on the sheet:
LTC6803-4
